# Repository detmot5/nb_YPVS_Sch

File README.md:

# Schematic and PCB for nb-YPVS

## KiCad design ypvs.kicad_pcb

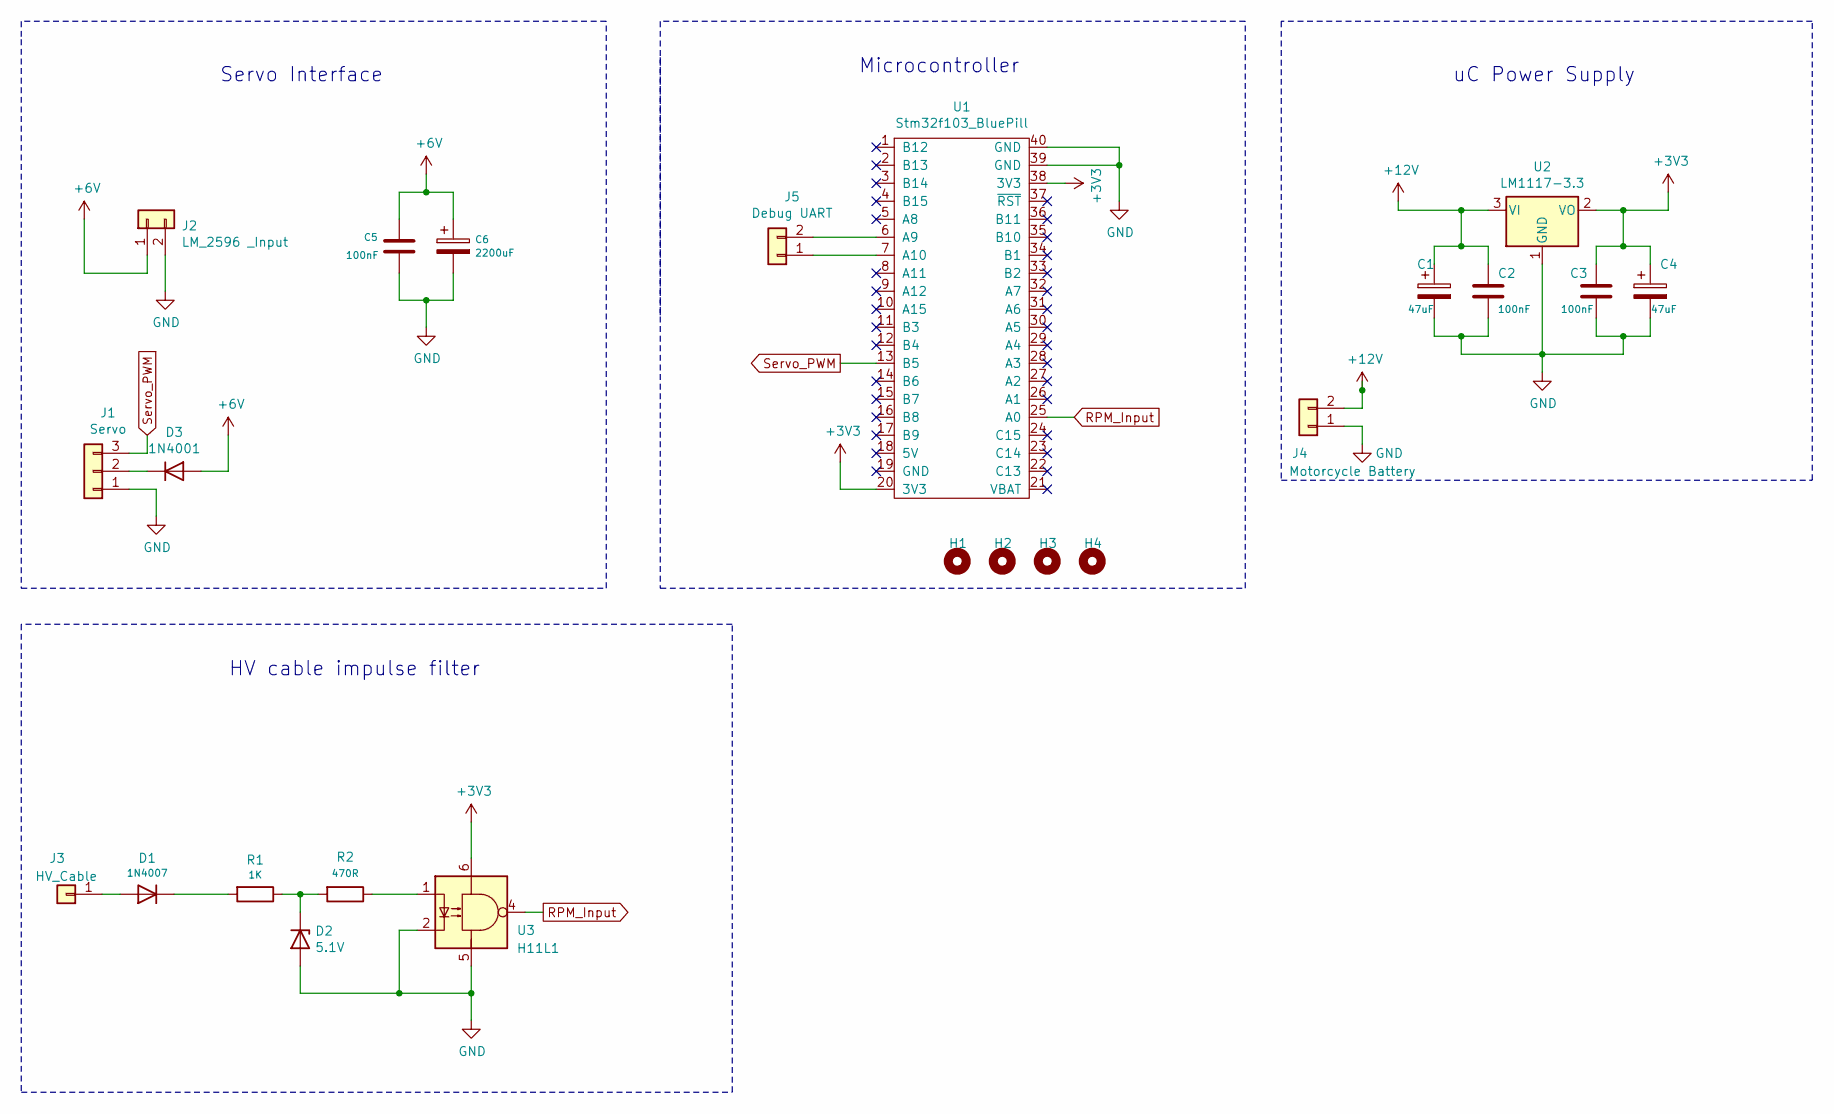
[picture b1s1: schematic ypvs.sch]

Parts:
C1, C4: 47uF; CP_Radial_D5.0mm_P2.00mm
C2, C3, C5: 100nF; C_Disc_D3.0mm_W1.6mm_P2.50mm
C6: 2200uF; CP_Radial_D10.0mm_P5.00mm
D1: 1N4007; D_A-405_P7.62mm_Horizontal
D2: 5.1V; D_A-405_P7.62mm_Horizontal
D3: 1N4001; D_A-405_P7.62mm_Horizontal
H1, H2, H3, H4: MountingHole; MountingHole_2.7mm_M2.5
J1: Servo; PinHeader_1x03_P2.54mm_Horizontal
J2: LM_2596 _Input; PinHeader_1x02_P2.54mm_Vertical
J3: HV_Cable; PinHeader_1x01_P2.54mm_Horizontal
J4: Motorcycle Battery; PinHeader_1x02_P2.54mm_Vertical
J5: Debug UART; PinHeader_1x02_P2.54mm_Vertical
R1: 1K; R_Axial_DIN0207_L6.3mm_D2.5mm_P7.62mm_Horizontal
R2: 470R; R_Axial_DIN0207_L6.3mm_D2.5mm_P7.62mm_Horizontal
U1: Stm32f103_BluePill; DIP-40_W15.24mm_LongPads
U2: LM1117-3.3; SOT-223-3_TabPin2
U3: H11L1; DIP-6_W7.62mm

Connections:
+3V3: C3.1, C4.1, U1.20 (3V3), U1.38 (3V3), U2.2 (VO), U3.6
+6V: C5.2, C6.1, D3.2 (A), J2.1
+12V: C1.1, C2.1, J4.2, U2.3 (VI)
GND: C1.2, C2.2, C3.2, C4.2, C5.1, C6.2, D2.2 (A), J1.1, J2.2, J4.1, U1.39 (GND), U1.40 (GND), U2.1 (GND), U3.2, U3.5
unnamed: D1.1 (K), R1.2
unnamed: D1.2 (A), J3.1
unnamed: D2.1 (K), R1.1, R2.2
unnamed: D3.1 (K), J1.2
unnamed: J5.1, U1.7 (A10)
unnamed: J5.2, U1.6 (A9)
unnamed: R2.1, U3.1
RPM_Input: U1.25 (A0), U3.4
Servo_PWM: J1.3, U1.13 (B5)

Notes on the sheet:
uC Power Supply
Microcontroller
Servo Interface
HV cable impulse filter

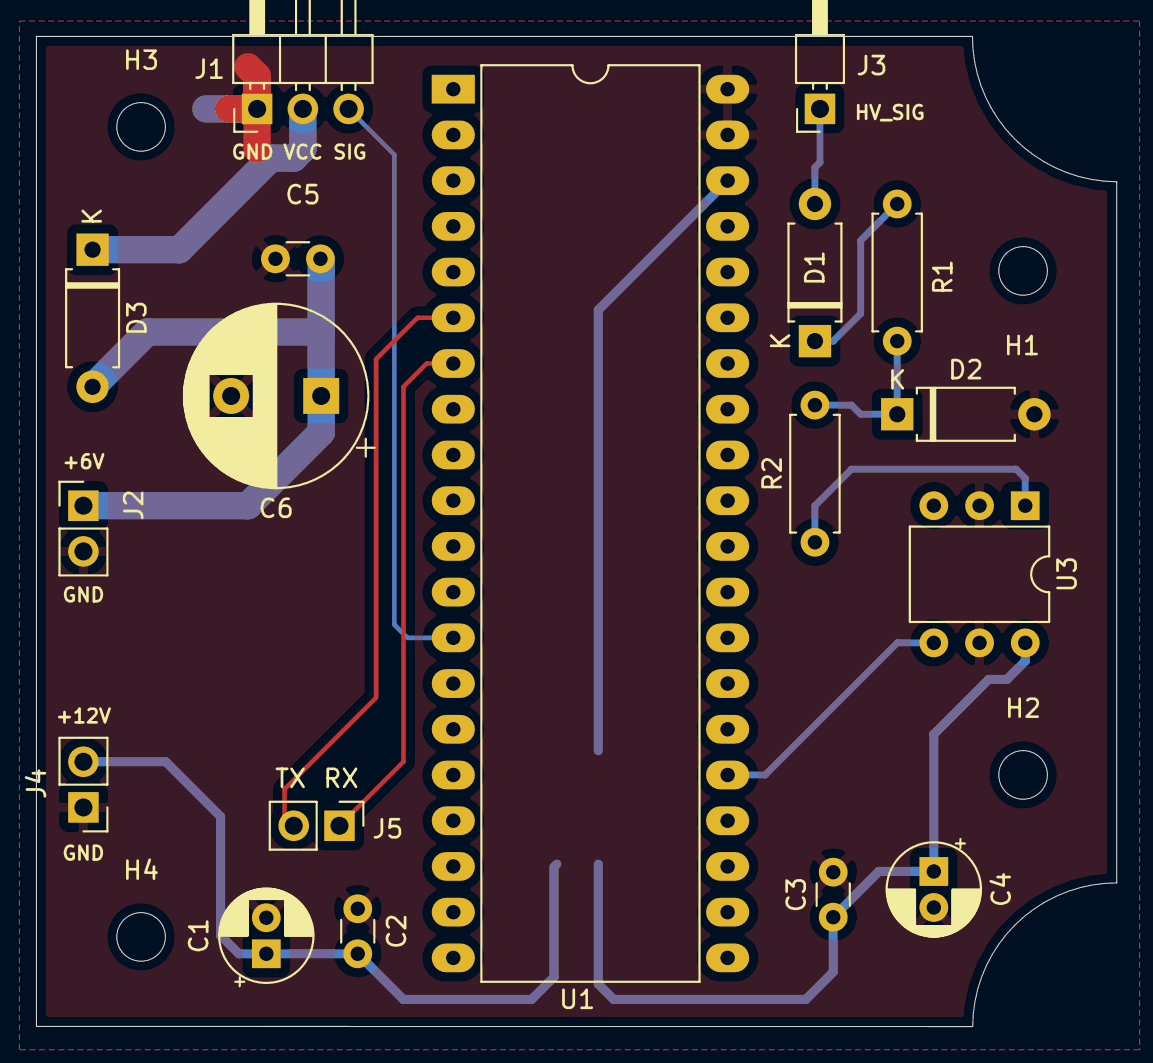
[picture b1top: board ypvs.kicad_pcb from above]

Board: 2 copper layers, 60.0 x 55.0 mm, 23 parts (1 on the bottom side), 13 nets.

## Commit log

2020-08-27 initial
2020-08-27 added readme
2020-08-27 changed bluepill lib added pcb
2020-08-28 added pcb outline and mounting holes
2020-08-28 Changed bluepill symbol
2020-08-29 Added PCB traces
2020-08-29 Fixed outline bug, added pin labels
2020-08-29 Final v01
